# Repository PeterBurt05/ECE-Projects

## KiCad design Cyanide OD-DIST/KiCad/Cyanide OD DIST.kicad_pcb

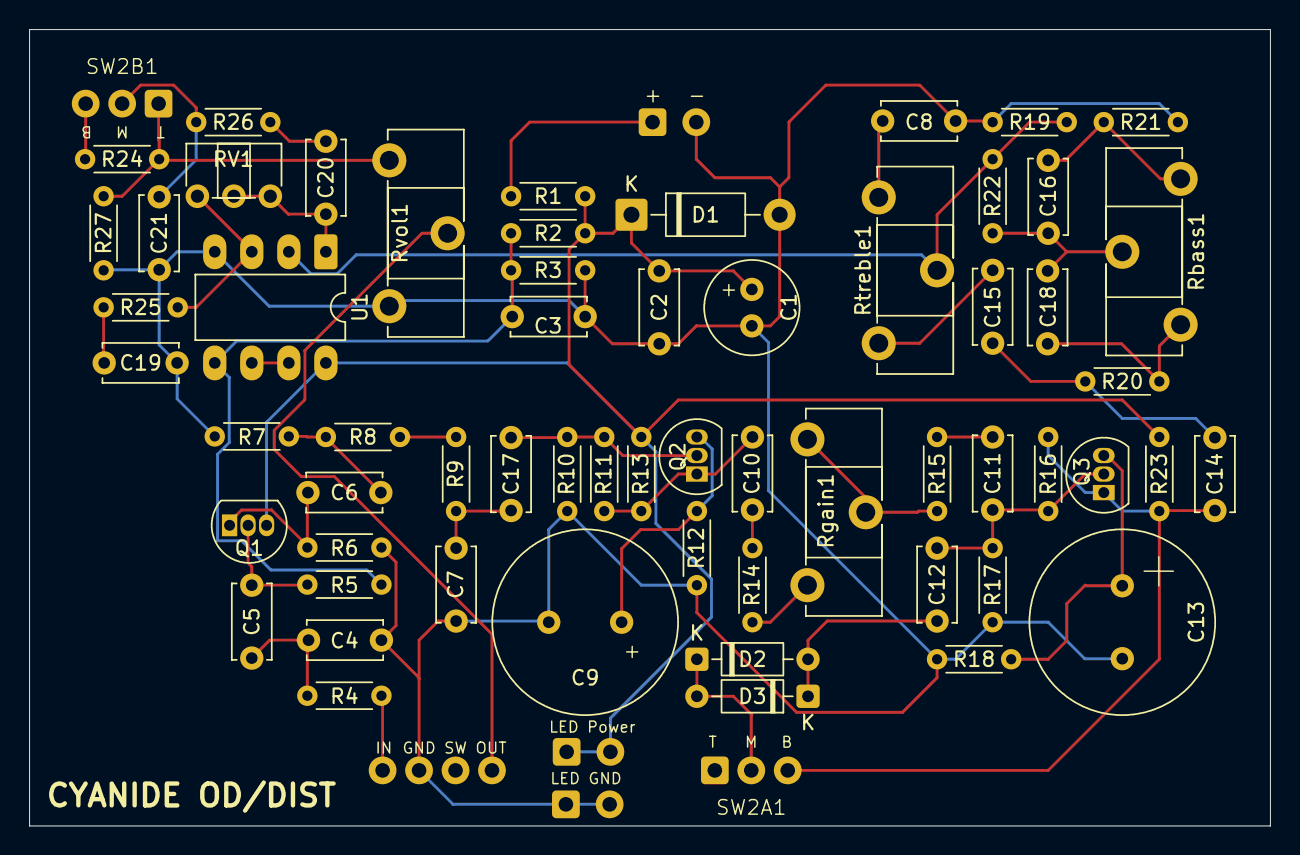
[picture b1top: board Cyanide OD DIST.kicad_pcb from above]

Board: 2 copper layers, 85.1 x 54.6 mm, 62 parts (0 on the bottom side), 36 nets.

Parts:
C1: 100uF; C_Radial_D6.3mm_H11.0mm_P2.50mm
C2, C5, C10, C11, C12, C14: 100nF; C_Disc_D5.0mm_W2.5mm_P5.00mm
C3, C6, C19, C20, C21: 1uF; C_Disc_D5.0mm_W2.5mm_P5.00mm
C4, C7: 100pF; C_Disc_D5.0mm_W2.5mm_P5.00mm
C8, C16: 4.7nF; C_Disc_D5.0mm_W2.5mm_P5.00mm
C9, C13: 20uF; C_Radial_D12.5mm_H25.0mm_P5.00mm
C15: 430pF; C_Disc_D5.0mm_W2.5mm_P5.00mm
C17: 22nF; C_Disc_D5.0mm_W2.5mm_P5.00mm
C18: 220pF; C_Disc_D5.0mm_W2.5mm_P5.00mm
D1: 1N4002; D_DO-41_SOD81_P10.16mm_Horizontal
D2, D3: 1N4148; D_DO-35_SOD27_P7.62mm_Horizontal
Q1, Q2, Q3: S8050; TO-92L_Inline
R1: 10R; R_Axial_DIN0204_L3.6mm_D1.6mm_P5.08mm_Horizontal
R2, R3, R10, R17, R20: 100k; R_Axial_DIN0204_L3.6mm_D1.6mm_P5.08mm_Horizontal
R4, R9: 1k; R_Axial_DIN0204_L3.6mm_D1.6mm_P5.08mm_Horizontal
R5: 470k; R_Axial_DIN0204_L3.6mm_D1.6mm_P5.08mm_Horizontal
R6, R7, R14, R15, R21: 10k; R_Axial_DIN0204_L3.6mm_D1.6mm_P5.08mm_Horizontal
R8, R12, R18, R26: 100; R_Axial_DIN0204_L3.6mm_D1.6mm_P5.08mm_Horizontal
R11, R16, R19, R24, R27: 1M; R_Axial_DIN0204_L3.6mm_D1.6mm_P5.08mm_Horizontal
R13, R23: 20k; R_Axial_DIN0204_L3.6mm_D1.6mm_P5.08mm_Horizontal
R22: 200k; R_Axial_DIN0204_L3.6mm_D1.6mm_P5.08mm_Horizontal
R25: 4.7k; R_Axial_DIN0204_L3.6mm_D1.6mm_P5.08mm_Horizontal
RV1: 50k; Potentiometer_ACP_CA6-H2,5_Horizontal
Rbass1: 1MegA; Potentiometer_ACP_CA14-H4_Horizontal
Rgain1: 500kA; Potentiometer_ACP_CA14-H4_Horizontal
Rtreble1: 500kA; Potentiometer_ACP_CA14-H4_Horizontal
Rvol1: 250kA; Potentiometer_ACP_CA14-H4_Horizontal
SW2A1: EG1218; SW
SW2B1: SW
U1: TL072; DIP-8_W7.62mm_LongPads

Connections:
+4.5V: C3.1, R2.1, R3.2, R5.2, U1.5 (+)
+9V: C1.1, C2.1, D1.1 (K), Q1.1 (C), R1.2, R2.2, R13.1, R23.1, U1.8 (V+)
Buffer_out: R8.2, R9.1
Dist_out: C14.1, C18.2, R20.2
GND: C1.2, C2.2, C3.2, C4.2, C7.2, C8.1, C9.2, C13.2, C19.1, C21.1, D1.2 (A), R3.1, R6.2, R7.2, R10.1, R12.1, R17.1, R18.1, R19.1, R21.1, R27.1, Rvol1.3, U1.4 (V-)
unnamed: C4.1, C5.2, R4.1
unnamed: C6.1, R7.1, R8.1
unnamed: C8.2, Rtreble1.1
unnamed: C10.2, R14.1
unnamed: C11.2, R15.2
unnamed: C15.1, R20.1, Rbass1.1
unnamed: C15.2, C16.2, R22.2, Rbass1.2
unnamed: C16.1, R21.2, Rbass1.3
unnamed: C7.1, C17.1, R9.2
unnamed: C18.1, Rtreble1.3
unnamed: C19.2, R25.2
unnamed: C20.1, R26.2
unnamed: C20.2, RV1.2, RV1.3, U1.1
unnamed: C21.2, R26.1, SW2B1.2
unnamed: C12.1, D2.2 (A), D3.1 (K)
unnamed: D2.1 (K), D3.2 (A), SW2A1.2
unnamed: C5.1, Q1.2 (B), R5.1
unnamed: C6.2, Q1.3 (E), R6.1
unnamed: C17.2, Q2.2 (B), R10.2, R11.1
unnamed: C10.1, Q2.1 (C), R11.2, R13.2
unnamed: C9.1, Q2.3 (E), R12.2
unnamed: C11.1, C12.2, Q3.2 (B), R16.1, R17.2
unnamed: C14.2, Q3.1 (C), R16.2, R23.2, SW2A1.3
unnamed: C13.1, Q3.3 (E), R18.2
unnamed: R14.2, Rgain1.3
unnamed: R15.1, Rgain1.1, Rgain1.2
unnamed: R24.1, R27.2, Rvol1.1, SW2B1.1
unnamed: R24.2, SW2B1.3
unnamed: R25.1, RV1.1, U1.3 (+)
unnamed: R19.2, R22.1, Rtreble1.2, U1.2 (-)
unnamed: U1.6 (-), U1.7

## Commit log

2026-05-28 chorus project
2026-05-28 added distortion project files
2026-05-28 added gitignore file
2026-05-28 removed extra files from dist project
2026-05-28 modified gitignore to include LTspice files, added oscillator demo
2026-05-28 added Boss CE-2 LFO demo
2026-05-28 reorganized files
2026-05-28 added wein bridge demo and sawtooth demo
2026-05-30 added an inverter to the sawtooth demo
2026-06-03 updated Sawtooth demo to include asymmetrical timing example for sine wave generation
2026-06-05 updated wein bridge demo with test component values
2026-06-05 started draft for chorus design
2026-06-08 testing
2026-06-08 removed test file
2026-06-08 LFO demo added
2026-06-09 editted some oscillator demos
2026-06-10 updated gitignore to whitelist .PDF files in documents folder of Chorus pedal
2026-06-10 added documents to chorus pedal
2026-06-10 updated demo files
